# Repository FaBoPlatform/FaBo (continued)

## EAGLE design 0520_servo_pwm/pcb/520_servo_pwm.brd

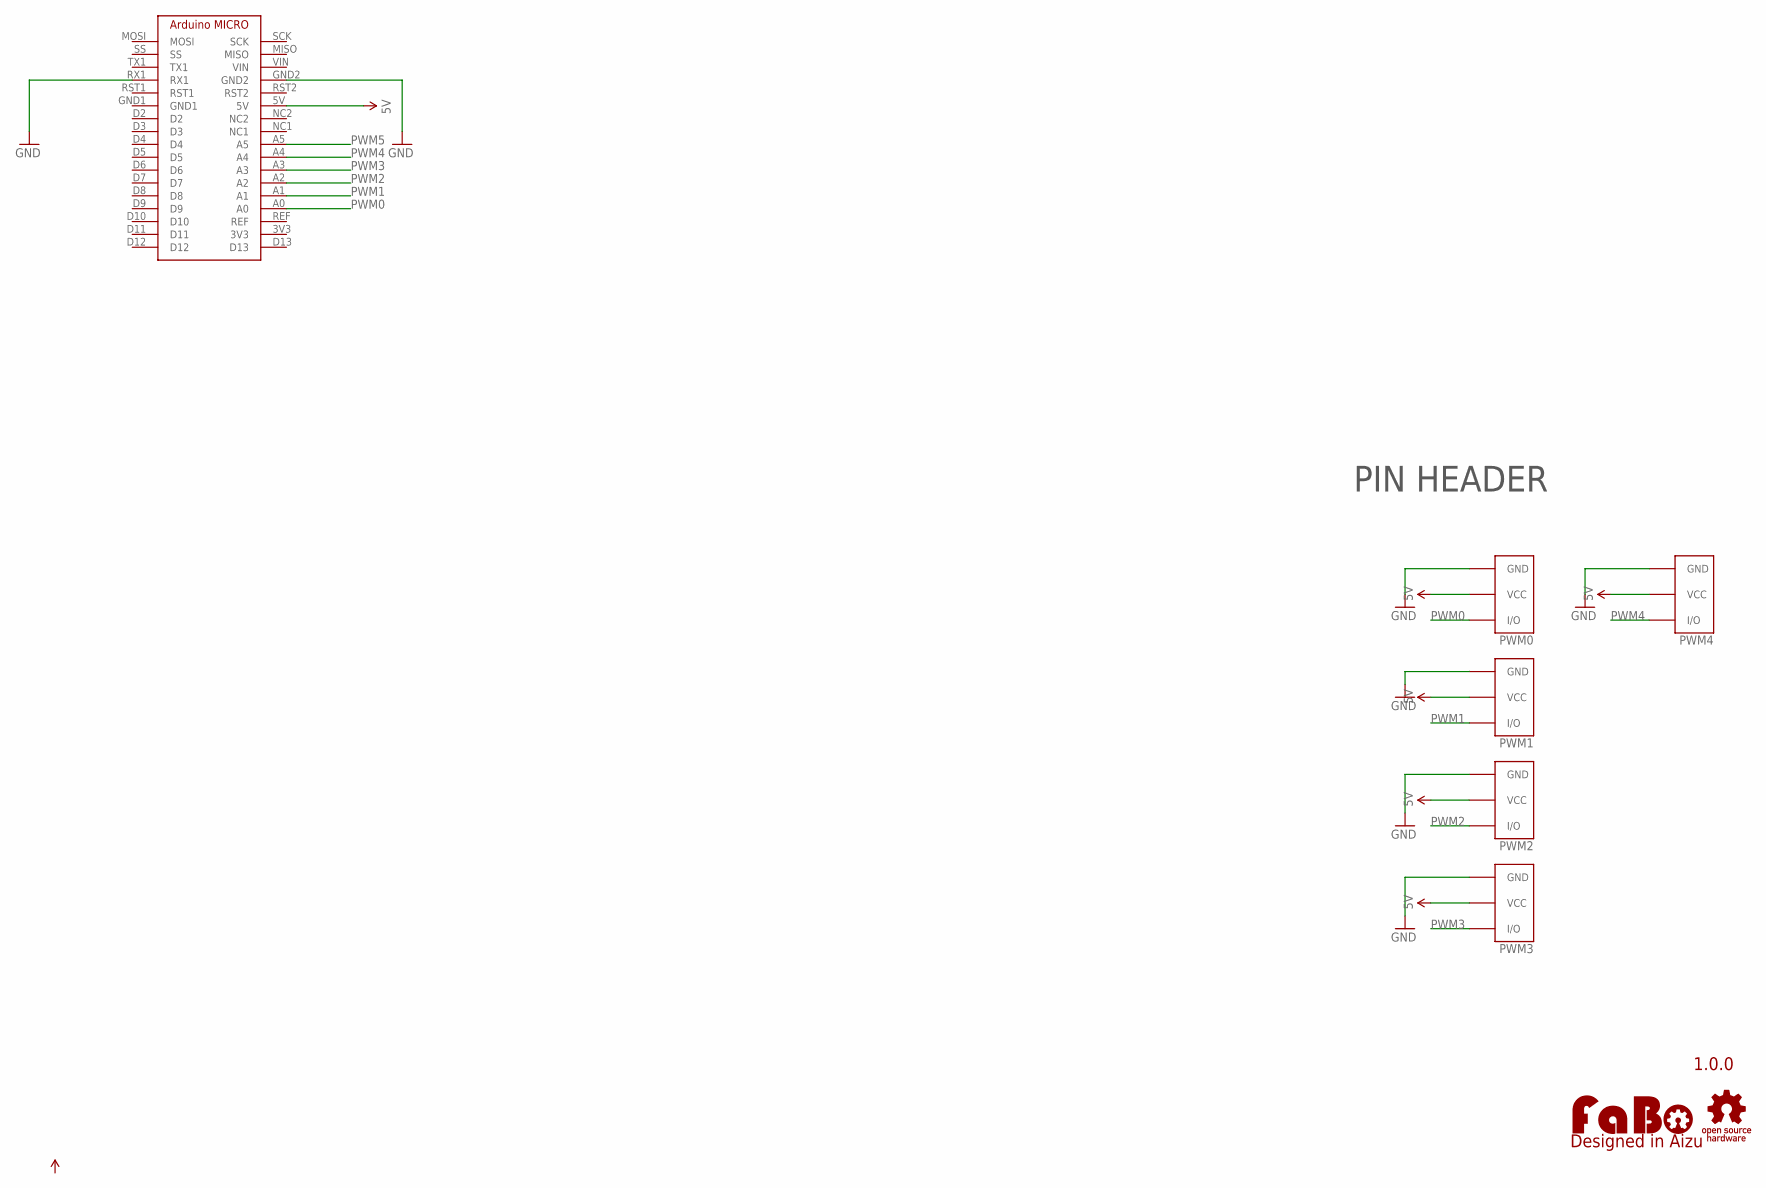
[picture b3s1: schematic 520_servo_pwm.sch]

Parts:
LOGO1: LOGO_FABO-M_BOTTOM; LOGO_FABO_M_BOTTOM
PWM0, PWM1, PWM2, PWM3, PWM4: FABO_BRICK_3PIN-HEADER; FABO_BRICK_3PIN_HEADER
U$2: ARDUINO_MICRO
U$3: LOGO_OSHW-M_BOTTOM; LOGO_OSHW_M_BOTTOM

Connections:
5V: PWM0.VCC, PWM1.VCC, PWM2.VCC, PWM3.VCC, PWM4.VCC, U$2.5V
GND: PWM0.GND, PWM1.GND, PWM2.GND, PWM3.GND, PWM4.GND, U$2.GND2, U$2.RX1
PWM0: PWM0.I/O, U$2.A0
PWM1: PWM1.I/O, U$2.A1
PWM2: PWM2.I/O, U$2.A2
PWM3: PWM3.I/O, U$2.A3
PWM4: PWM4.I/O, U$2.A4
PWM5: U$2.A5

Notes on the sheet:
1.0.0
PIN HEADER

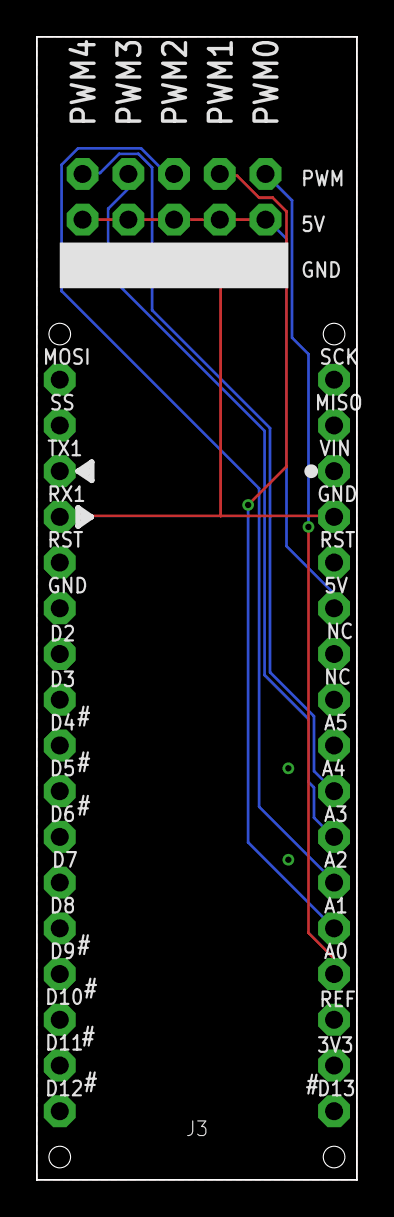
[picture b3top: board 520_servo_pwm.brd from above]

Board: 2 copper layers, 17.8 x 63.5 mm, 8 parts (0 on the bottom side), 7 nets.

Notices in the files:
parts and their libraries:
FaBo-Template: Released under the Creative Commons Attribution-ShareAlike 4.0 License
https://creativecommons.org/licenses/by-sa/4.0
FaBo-etc: Released under the Creative Commons
